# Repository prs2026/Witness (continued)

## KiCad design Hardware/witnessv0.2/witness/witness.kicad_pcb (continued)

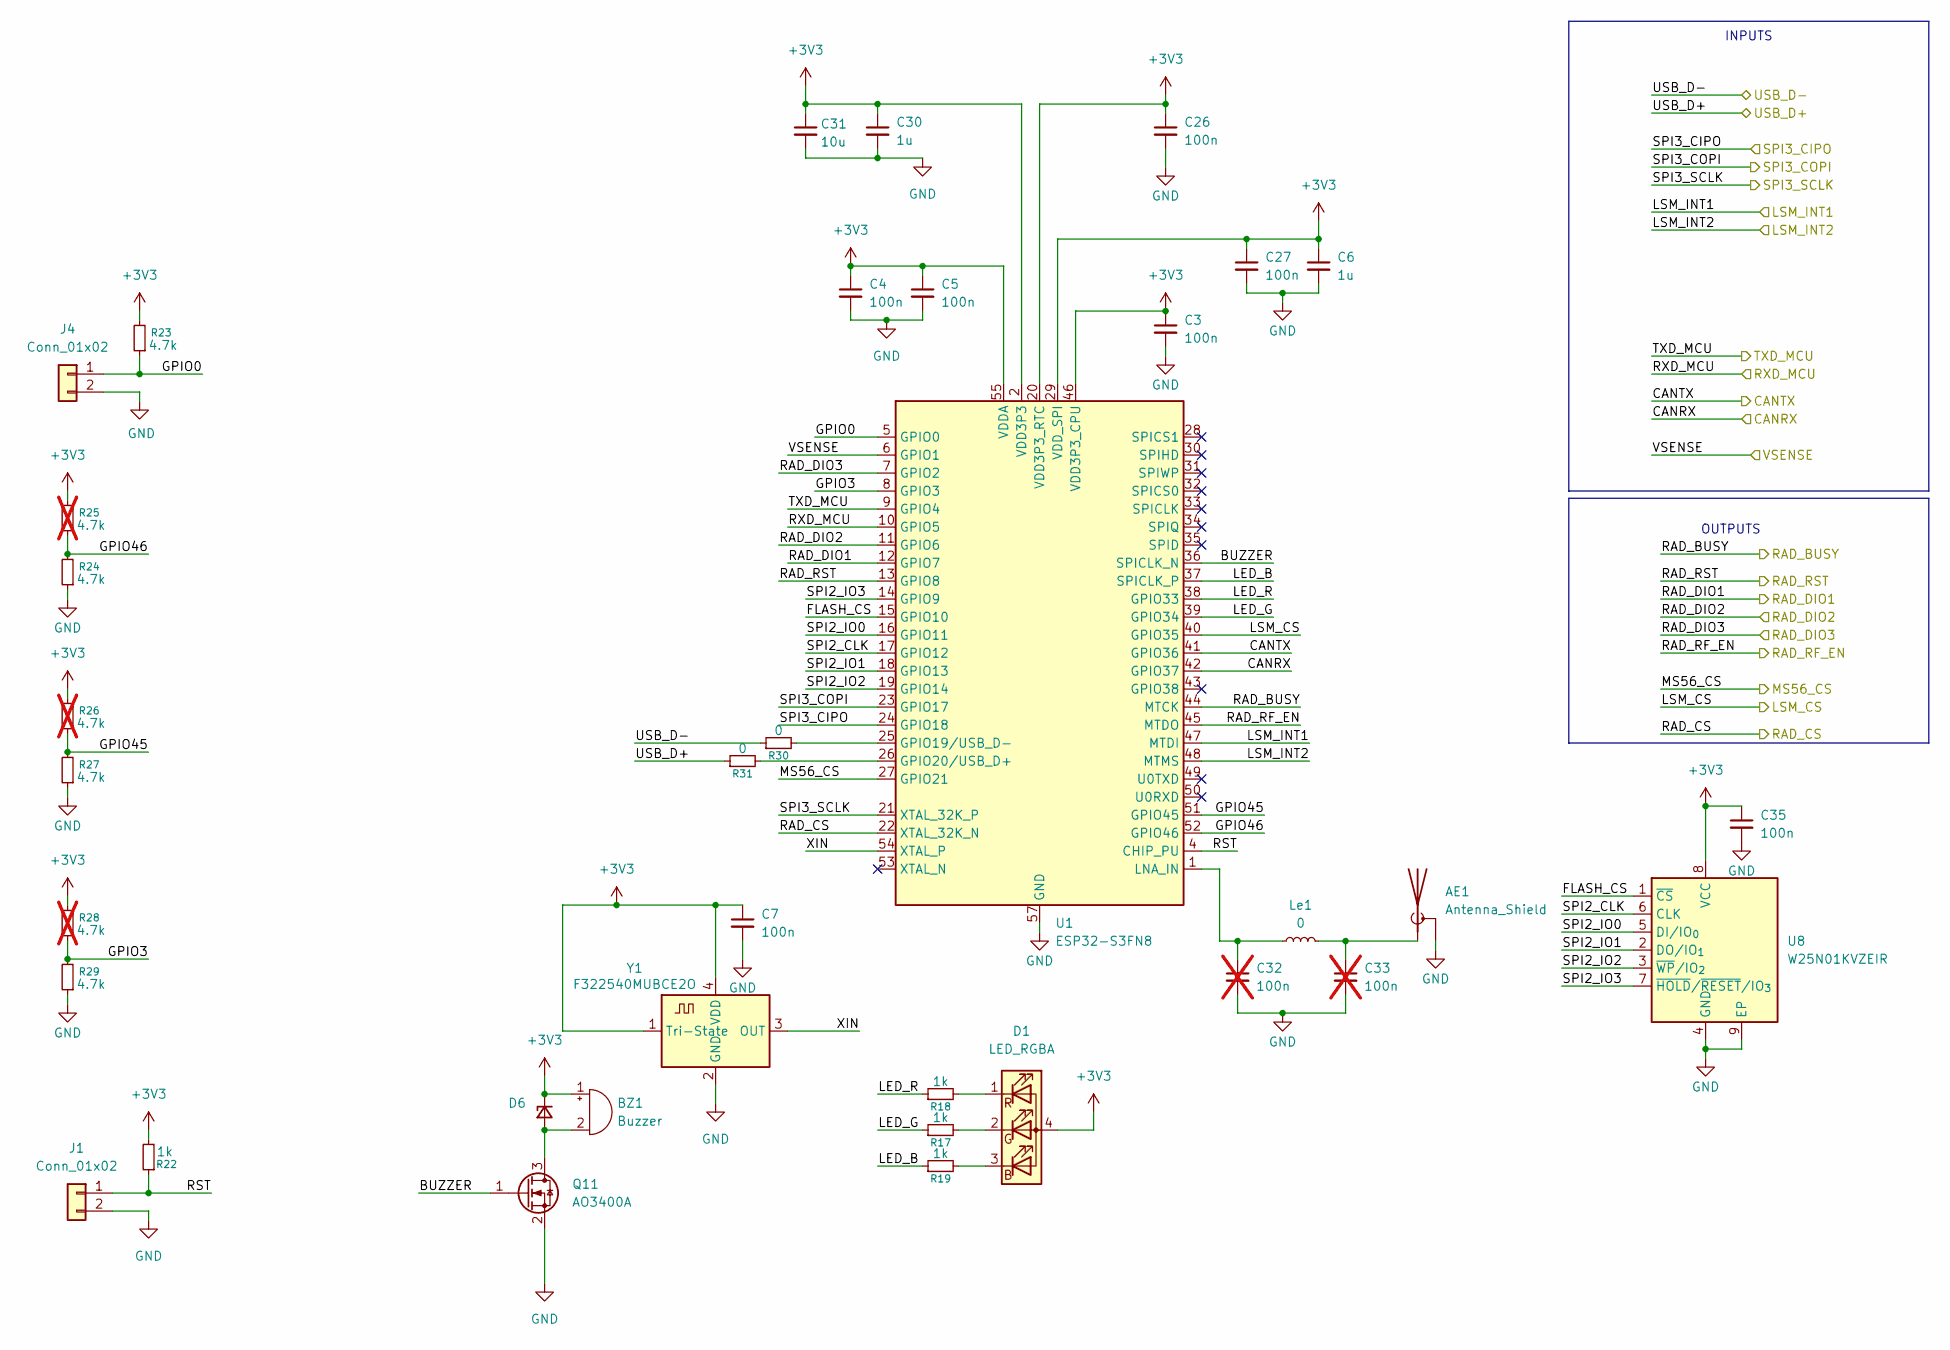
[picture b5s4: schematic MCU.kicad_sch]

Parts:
AE1: Antenna_Shield; U.FL_Molex_MCRF_73412-0110_Vertical
BZ1: Buzzer; OWMB-505020S-40-12D
C3, C4, C5, C7, C26, C27, C35: 100n; C_0402_1005Metric; LCSC_Part C307331
C6, C30: 1u; C_0402_1005Metric; LCSC_Part C52923
C31: 10u; C_0603_1608Metric; LCSC_Part C96446
C32, C33: 100n; C_0402_1005Metric; LCSC_Part C307331; not fitted
D1: LED_RGBA; 0603x2 RGB
D6: BZX584C10; D_SOD-523; LCSC_Part C22395577
J1, J4: Conn_01x02; SolderJumper-2_P1.3mm_Open_RoundedPad1.0x1.5mm
Le1: 0; L_0402_1005Metric
Q11: AO3400A; SOT-23; LCSC_Part C20917
R17, R18, R19, R22: 1k; R_0402_1005Metric; LCSC_Part C11702
R23, R24, R27, R29: 4.7k; R_0402_1005Metric; LCSC_Part C25900
R25, R26, R28: 4.7k; R_0402_1005Metric; LCSC_Part C25900; not fitted
R30, R31: 0; R_0402_1005Metric; LCSC_Part C17168
U1: ESP32-S3FN8; QFN-56-1EP_7x7mm_P0.4mm_EP4x4mm; LCSC_Part C2913196
U8: W25N01KVZEIR; WSON-8-1EP_8x6mm_P1.27mm_EP3.4x4.3mm; LCSC_Part C22472329
Y1: F322540MUBCE2O; Oscillator_SMD_Abracon_ASCO-4Pin_1.6x1.2mm; LCSC_Part C5917310

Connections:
+3V3: BZ1.1 (+), C3.1, C4.1, C5.1, C6.1, C7.1, C26.1, C27.1, C30.1, C31.1, C35.1, D1.4 (A), D6.1 (K), R22.2, R23.2, R25.2, R26.2, R28.2, U1.2 (VDD3P3), U1.3 (VDD3P3), U1.20 (VDD3P3_RTC), U1.29 (VDD_SPI), U1.46 (VDD3P3_CPU), U1.55 (VDDA), U1.56 (VDDA), U8.8 (VCC), Y1.1 (Tri-State), Y1.4 (VDD); also elsewhere on the board
/IO/USB_D+: R31.1; also elsewhere on the board
/IO/USB_D-: R30.1; also elsewhere on the board
/MCU/BUZZER: Q11.1 (G), U1.36 (SPICLK_N)
/MCU/CANRX: U1.42 (GPIO37); also elsewhere on the board
/MCU/CANTX: U1.41 (GPIO36); also elsewhere on the board
/MCU/FLASH_CS: U1.15 (GPIO10), U8.1 (~CS)
/MCU/GPIO0: J4.1, R23.1, U1.5 (GPIO0)
/MCU/GPIO3: R28.1, R29.2, U1.8 (GPIO3)
/MCU/GPIO45: R26.1, R27.2, U1.51 (GPIO45)
/MCU/GPIO46: R24.2, R25.1, U1.52 (GPIO46)
/MCU/LED_B: R19.1, U1.37 (SPICLK_P)
/MCU/LED_G: R17.1, U1.39 (GPIO34)
/MCU/LED_R: R18.1, U1.38 (GPIO33)
/MCU/LSM_CS: U1.40 (GPIO35); also elsewhere on the board
/MCU/LSM_INT1: U1.47 (MTDI); also elsewhere on the board
/MCU/LSM_INT2: U1.48 (MTMS); also elsewhere on the board
/MCU/MS56_CS: U1.27 (GPIO21); also elsewhere on the board
/MCU/RAD_BUSY: U1.44 (MTCK); also elsewhere on the board
/MCU/RAD_CS: U1.22 (XTAL_32K_N); also elsewhere on the board
/MCU/RAD_DIO1: U1.12 (GPIO7); also elsewhere on the board
/MCU/RAD_DIO2: U1.11 (GPIO6); also elsewhere on the board
/MCU/RAD_DIO3: U1.7 (GPIO2); also elsewhere on the board
/MCU/RAD_RF_EN: U1.45 (MTDO); also elsewhere on the board
/MCU/RAD_RST: U1.13 (GPIO8); also elsewhere on the board
/MCU/RST: J1.1, R22.1, U1.4 (CHIP_PU)
/MCU/RXD_MCU: U1.10 (GPIO5); also elsewhere on the board
/MCU/SPI2_CLK: U1.17 (GPIO12), U8.6 (CLK)
/MCU/SPI2_IO0: U1.16 (GPIO11), U8.5 (DI/IO_{0})
/MCU/SPI2_IO1: U1.18 (GPIO13), U8.2 (DO/IO_{1})
/MCU/SPI2_IO2: U1.19 (GPIO14), U8.3 (~WP/IO_{2})
/MCU/SPI2_IO3: U1.14 (GPIO9), U8.7 (~HOLD/~RESET/IO_{3})
/MCU/SPI3_CIPO: U1.24 (GPIO18); also elsewhere on the board
/MCU/SPI3_COPI: U1.23 (GPIO17); also elsewhere on the board
/MCU/SPI3_SCLK: U1.21 (XTAL_32K_P); also elsewhere on the board
/MCU/TXD_MCU: U1.9 (GPIO4); also elsewhere on the board
/MCU/VSENSE: U1.6 (GPIO1); also elsewhere on the board
/MCU/XIN: U1.54 (XTAL_P), Y1.3 (OUT)
GND: AE1.2 (Shield), C3.2, C4.2, C5.2, C6.2, C7.2, C26.2, C27.2, C30.2, C31.2, C32.2, C33.2, C35.2, J1.2, J4.2, Q11.2 (S), R24.1, R27.1, R29.1, U1.57 (GND), U8.4 (GND), U8.9 (EP), Y1.2 (GND); also elsewhere on the board
unnamed: AE1.1 (A), C33.1, Le1.2
unnamed: BZ1.2 (-), D6.2 (A), Q11.3 (D)
unnamed: D1.3 (BK), R19.2
unnamed: D1.2 (GK), R17.2
unnamed: D1.1 (RK), R18.2
unnamed: R30.2, U1.25 (GPIO19/USB_D-)
unnamed: R31.2, U1.26 (GPIO20/USB_D+)
unnamed: C32.1, Le1.1, U1.1 (LNA_IN)

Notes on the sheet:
OUTPUTS
INPUTS

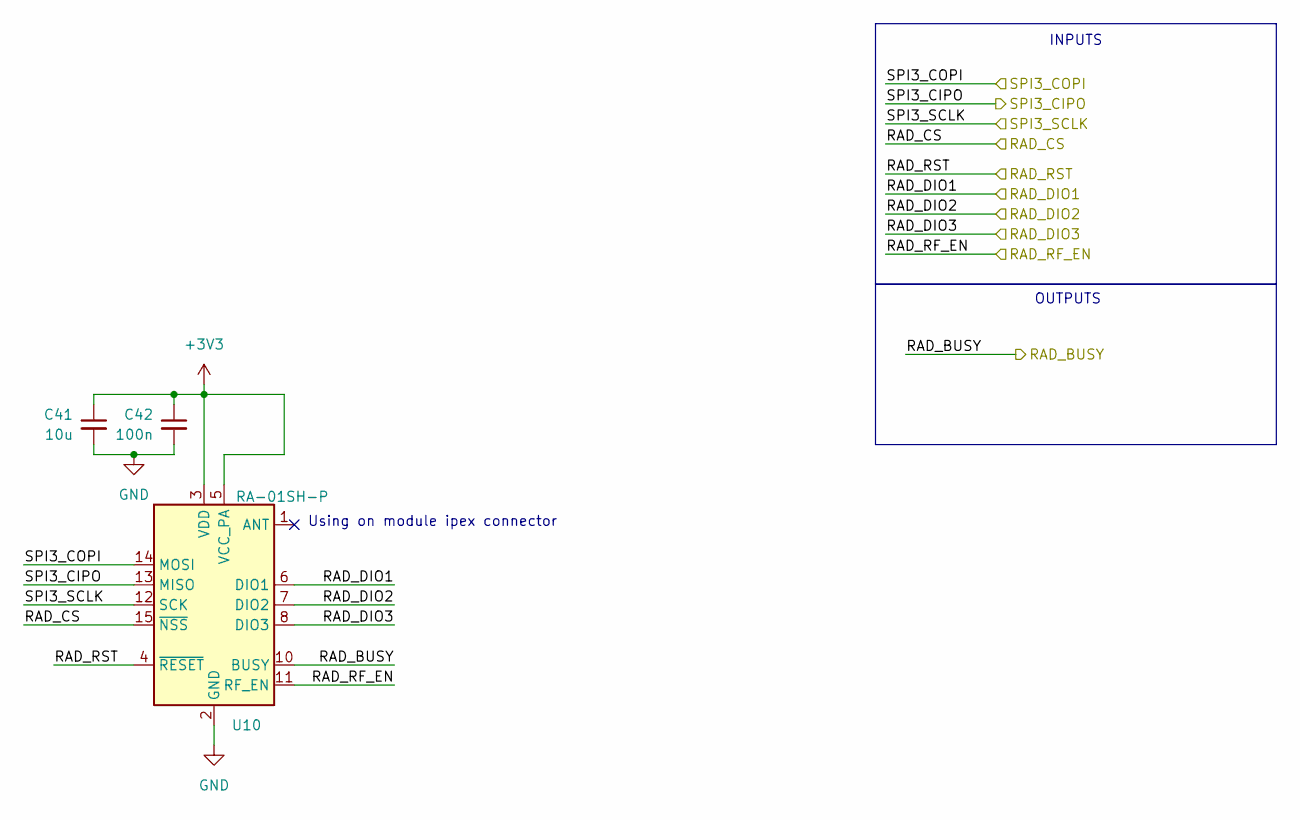
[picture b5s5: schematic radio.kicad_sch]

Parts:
C41: 10u; C_0603_1608Metric; LCSC_Part C96446
C42: 100n; C_0402_1005Metric; LCSC_Part C307331
U10: RA-01SH-P; Ai-Thinker-Ra-01-LoRa

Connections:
+3V3: C41.1, C42.1, U10.3 (VDD), U10.5 (VCC_PA); also elsewhere on the board
/MCU/RAD_BUSY: U10.10 (BUSY); also elsewhere on the board
/MCU/RAD_CS: U10.15 (~NSS); also elsewhere on the board
/MCU/RAD_DIO1: U10.6 (DIO1); also elsewhere on the board
/MCU/RAD_DIO2: U10.7 (DIO2); also elsewhere on the board
/MCU/RAD_DIO3: U10.8 (DIO3); also elsewhere on the board
/MCU/RAD_RF_EN: U10.11 (RF_EN); also elsewhere on the board
/MCU/RAD_RST: U10.4 (~RESET); also elsewhere on the board
/MCU/SPI3_CIPO: U10.13 (MISO); also elsewhere on the board
/MCU/SPI3_COPI: U10.14 (MOSI); also elsewhere on the board
/MCU/SPI3_SCLK: U10.12 (SCK); also elsewhere on the board
GND: C41.2, C42.2, U10.2 (GND), U10.9 (GND), U10.16 (GND); also elsewhere on the board

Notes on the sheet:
Using on module ipex connector
OUTPUTS
INPUTS

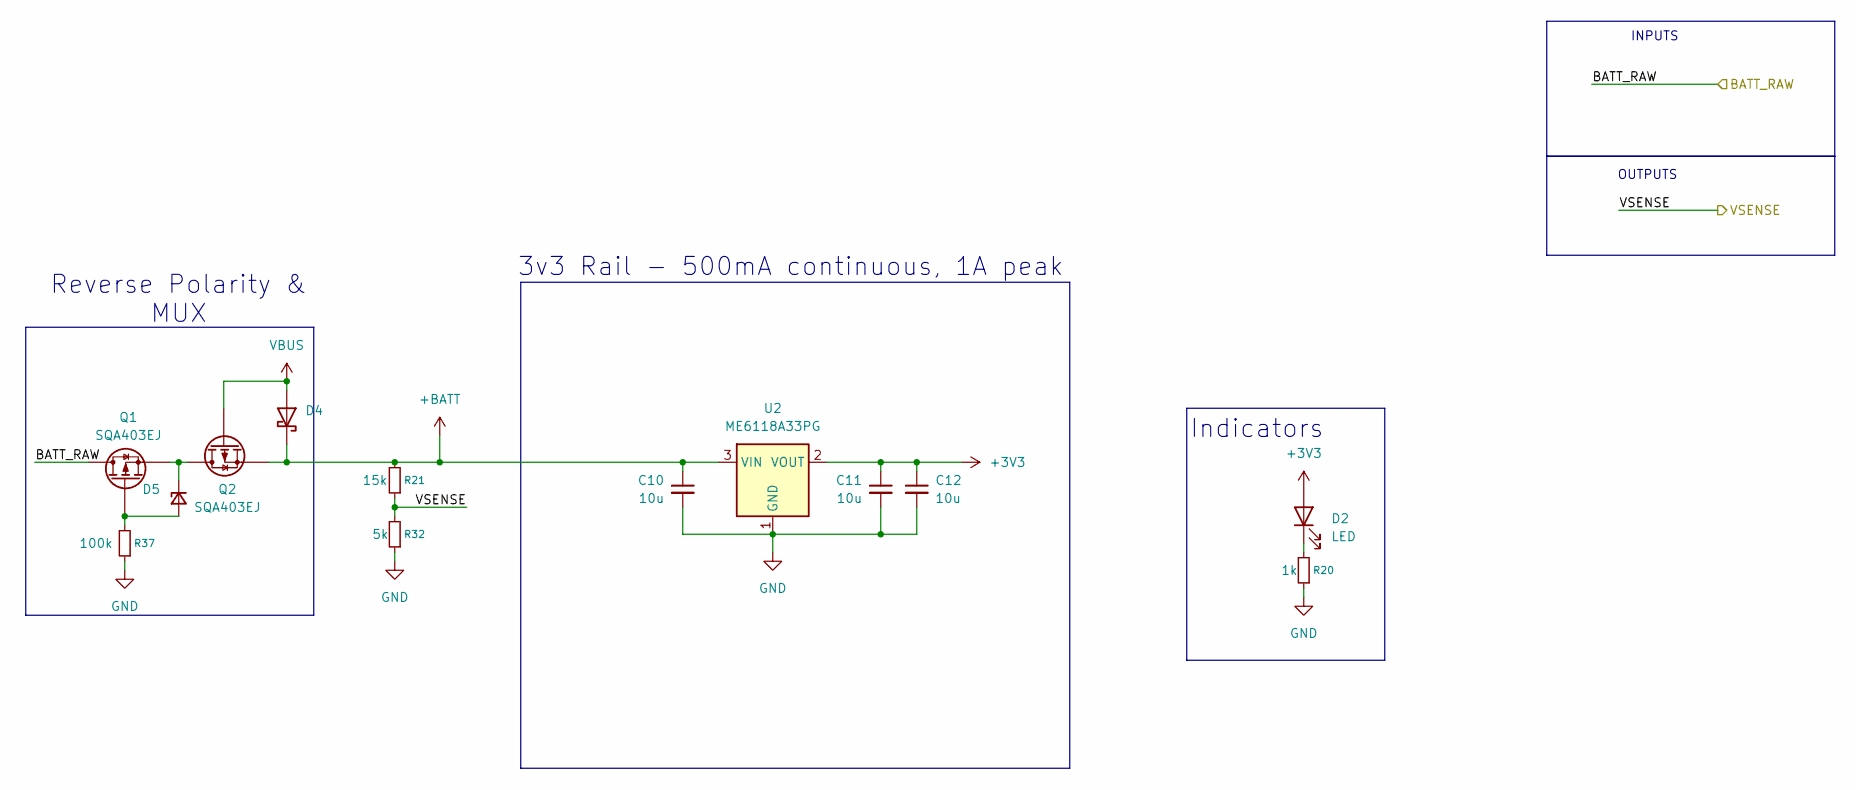
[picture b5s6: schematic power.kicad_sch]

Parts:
C10, C11, C12: 10u; C_0805_2012Metric; LCSC_Part C440198
D2: LED; LED_0603_1608Metric
D4: PMEG2020EH,115; D_SOD-123F; LCSC_Part C456104
D5: BZX584C10; D_SOD-523; LCSC_Part C22395577
Q1, Q2: SQA403EJ; Vishay_PowerPAK_SC70-6L_Single; LCSC_Part C7083947
R20: 1k; R_0402_1005Metric; LCSC_Part C11702
R21: 15k; R_0402_1005Metric
R32: 5k; R_0402_1005Metric
R37: 100k; R_0402_1005Metric
U2: ME6118A33PG; SOT-89-3; LCSC_Part C236721

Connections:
+3V3: C11.1, C12.1, D2.2 (A), U2.2 (VOUT); also elsewhere on the board
+BATT: C10.1, D4.1 (K), Q2.4 (S), R21.2, U2.3 (VIN)
/IO/BATT_RAW: Q1.1 (D); also elsewhere on the board
/MCU/VSENSE: R21.1, R32.2; also elsewhere on the board
GND: C10.2, C11.2, C12.2, R20.1, R32.1, R37.1, U2.1 (GND); also elsewhere on the board
unnamed: D2.1 (K), R20.2
unnamed: D5.2 (A), Q1.3 (G), R37.2
unnamed: D5.1 (K), Q1.4 (S), Q2.1 (D)
VBUS: D4.2 (A), Q2.3 (G); also elsewhere on the board

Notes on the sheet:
Indicators
OUTPUTS
INPUTS
Reverse Polarity & MUX
3v3 Rail - 500mA continuous, 1A peak

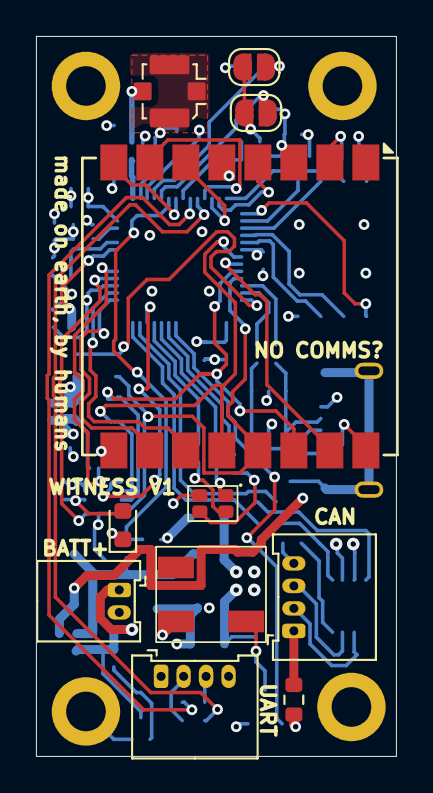
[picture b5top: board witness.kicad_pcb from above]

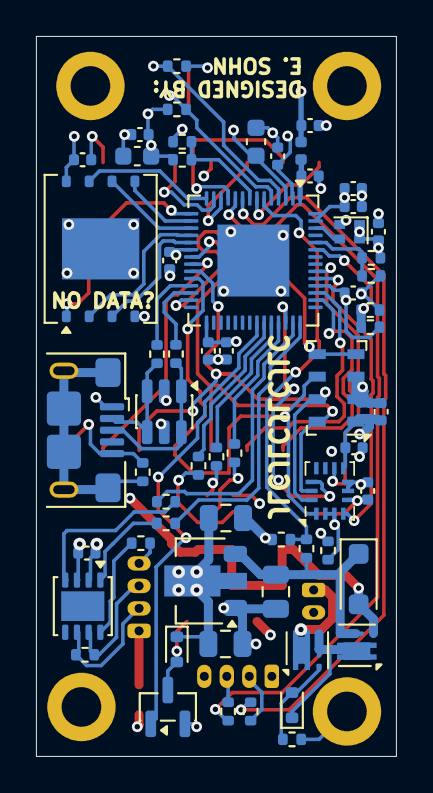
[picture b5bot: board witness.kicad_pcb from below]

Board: 4 copper layers, 20.0 x 40.0 mm, 76 parts (61 on the bottom side), 62 nets.

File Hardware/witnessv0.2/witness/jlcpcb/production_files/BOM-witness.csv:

Comment,Designator,Footprint,LCSC,Quantity
0,"R30,R31,R33,R34,R35,R36,R38,R51",R_0402_1005Metric,C17168,8
100n,"C26,C27,C28,C3,C35,C36,C37,C38,C4,C42,C5,C7",C_0402_1005Metric,C307331,12
10u,"C10,C11,C12",C_0805_2012Metric,C440198,3
10u,"C31,C41",C_0603_1608Metric,C96446,2
120,R39,R_0402_1005Metric,C25079,1
1k,"R17,R18,R19,R20,R22",R_0402_1005Metric,C11702,5
1u,"C30,C6",C_0402_1005Metric,C52923,2
4.7k,"R23,R24,R27,R29",R_0402_1005Metric,C25900,4
AO3400A,Q11,SOT-23,C20917,1
BZX584C10,"D5,D6",D_SOD-523,C22395577,2
ESP32-S3FN8,U1,QFN-56-1EP_7x7mm_P0.4mm_EP4x4mm,C2913196,1
F322540MUBCE2O,Y1,Oscillator_SMD_Abracon_ASCO-4Pin_1.6x1.2mm,C5917310,1
LSM6DSV320XTR,U4,Bosch_LGA-14_3x2.5mm_P0.5mm,C26633007,1
ME6118A33PG,U2,SOT-89-3,C236721,1
MS5607-02BA,U7,LGA-8_3x5mm_P1.25mm,C97627,1
"PMEG2020EH,115",D4,D_SOD-123F,C456104,1
SQA403EJ,"Q1,Q2",Vishay_PowerPAK_SC70-6L_Single,C7083947,2
TCAN1044A-Q1,U5,VSON-8-1EP_3x3mm_P0.65mm_EP1.65x2.4mm,C3234119,1
USBLC6-2SC6,U9,SOT-23-6,C7519,1
USB_B_Micro,J3,USB_Micro-B_Amphenol_10118193-0002LF_Horizontal,C132562,1
W25N01KVZEIR,U8,WSON-8-1EP_8x6mm_P1.27mm_EP3.4x4.3mm,C22472329,1
RA-01SH-P,U10,Ai-Thinker-Ra-01-LoRa,,1
Conn_01x02,J4,SolderJumper-2_P1.3mm_Open_RoundedPad1.0x1.5mm,,1
Conn_01x04,J5,Molex_MicroLock-2200980471-01x04-Horizontal,,1
Conn_01x02,J1,SolderJumper-2_P1.3mm_Open_RoundedPad1.0x1.5mm,,1
Conn_01x04,J6,Molex_MicroLock-2200980471-01x04-Horizontal,,1
MountingHole_Pad,H6,MountingHole_2.2mm_M2_DIN965_Pad,,1
MountingHole_Pad,H5,MountingHole_2.2mm_M2_DIN965_Pad,,1
LED_RGBA,D1,0603x2 RGB,,1
Conn_01x02,J2,Molex_Micro_Lock_2200980271_01x02_Horizontal,,1
MountingHole_Pad,H7,MountingHole_2.2mm_M2_DIN965_Pad,,1
Buzzer,BZ1,OWMB-505020S-40-12D,,1
LED,D2,LED_0603_1608Metric,,1
MountingHole_Pad,H4,MountingHole_2.2mm_M2_DIN965_Pad,,1
Antenna_Shield,AE1,U.FL_Molex_MCRF_73412-0110_Vertical,,1
15k,R21,R_0402_1005Metric,,1
100k,R37,R_0402_1005Metric,,1
5k,R32,R_0402_1005Metric,,1
0,R13,R_0603_1608Metric,,1
0,Le1,L_0402_1005Metric,,1

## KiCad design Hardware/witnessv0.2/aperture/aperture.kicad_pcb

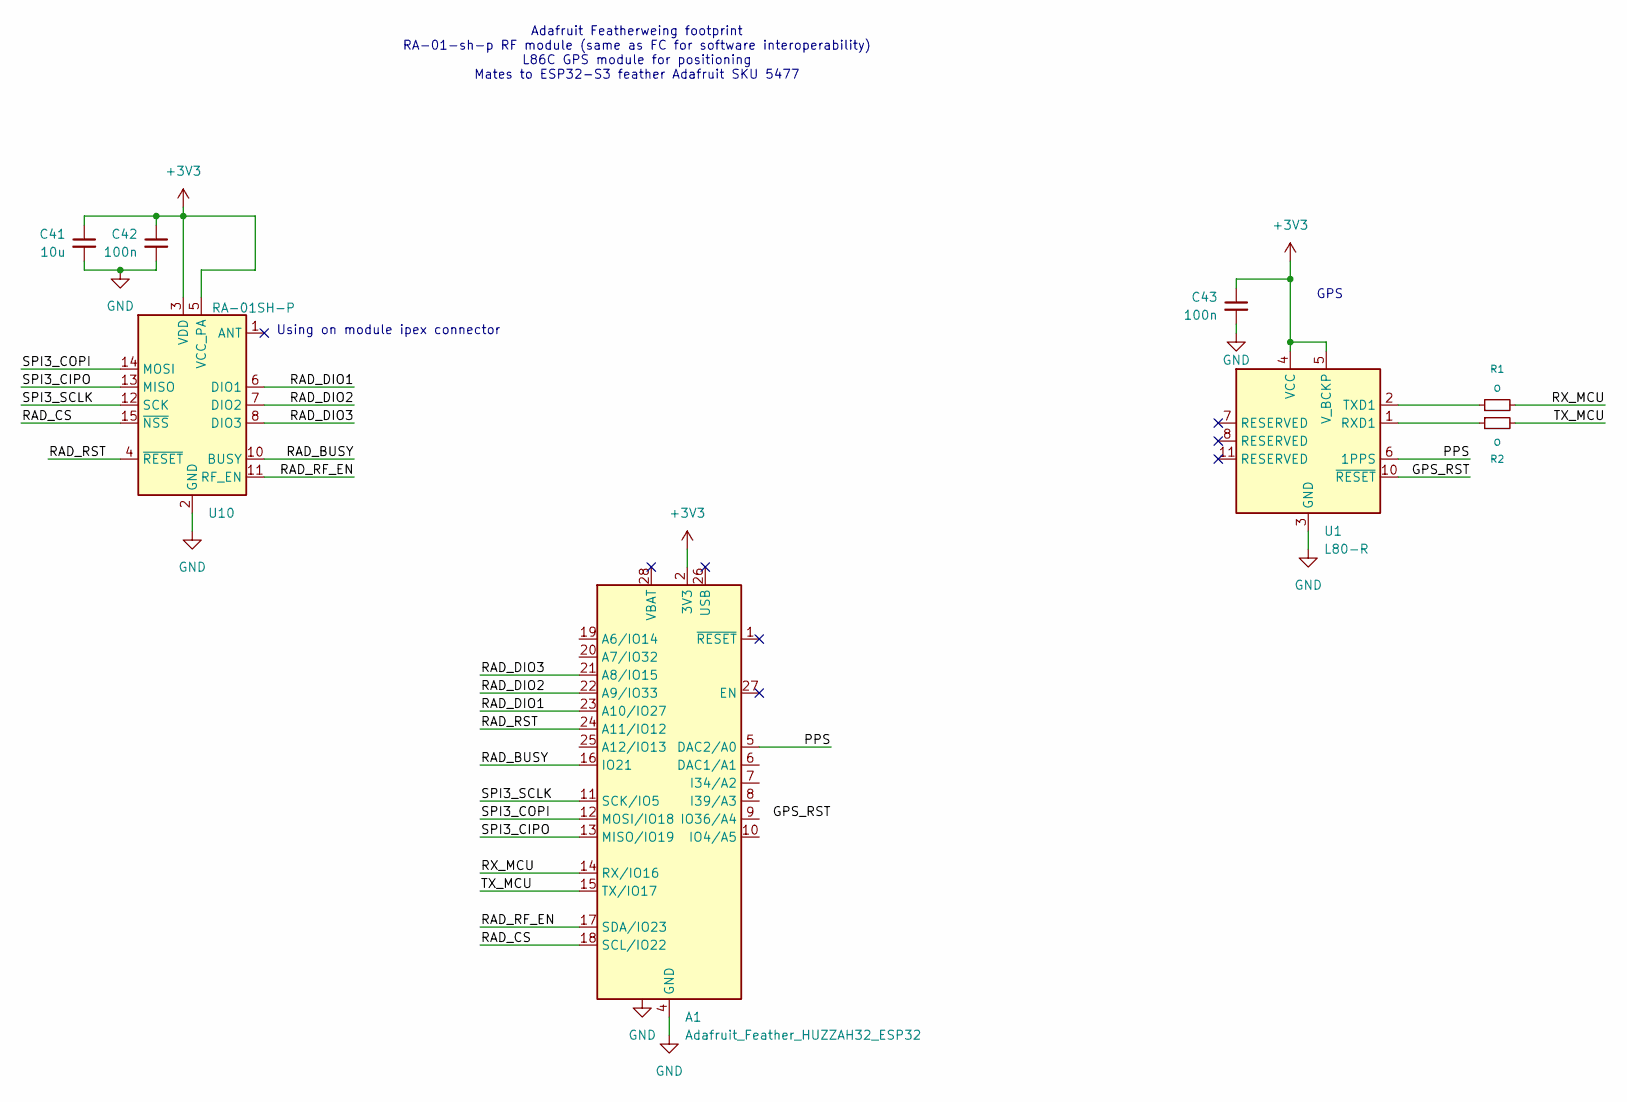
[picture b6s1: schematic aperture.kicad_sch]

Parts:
A1: Adafruit_Feather_HUZZAH32_ESP32; Adafruit_Feather
C41: 10u; C_0603_1608Metric; LCSC_Part C96446
C42, C43: 100n; C_0603_1608Metric; LCSC_Part C96446
R1, R2: o; R_0603_1608Metric
U1: L80-R; Quectel_L80-R
U10: RA-01SH-P; Ai-Thinker-Ra-01-LoRa

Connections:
+3V3: A1.2 (3V3), C41.1, C42.1, C43.1, U1.4 (VCC), U1.5 (V_BCKP), U10.3 (VDD), U10.5 (VCC_PA)
/GPS_RST: A1.9 (IO36/A4), U1.10 (~RESET)
/PPS: A1.5 (DAC2/A0), U1.6 (1PPS)
/RAD_BUSY: A1.16 (IO21), U10.10 (BUSY)
/RAD_CS: A1.18 (SCL/IO22), U10.15 (~NSS)
/RAD_DIO1: A1.23 (A10/IO27), U10.6 (DIO1)
/RAD_DIO2: A1.22 (A9/IO33), U10.7 (DIO2)
/RAD_DIO3: A1.21 (A8/IO15), U10.8 (DIO3)
/RAD_RF_EN: A1.17 (SDA/IO23), U10.11 (RF_EN)
/RAD_RST: A1.24 (A11/IO12), U10.4 (~RESET)
/RX_MCU: A1.14 (RX/IO16), R1.2
/SPI3_CIPO: A1.13 (MISO/IO19), U10.13 (MISO)
/SPI3_COPI: A1.12 (MOSI/IO18), U10.14 (MOSI)
/SPI3_SCLK: A1.11 (SCK/IO5), U10.12 (SCK)
/TX_MCU: A1.15 (TX/IO17), R2.2
GND: A1.4 (GND), C41.2, C42.2, C43.2, U1.3 (GND), U1.12 (GND), U10.2 (GND), U10.9 (GND), U10.16 (GND)
unnamed: R2.1, U1.1 (RXD1)
unnamed: R1.1, U1.2 (TXD1)

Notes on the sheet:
GPS
Using on module ipex connector
Adafruit Featherweing footprint RA-01-sh-p RF module (same as FC for software interoperability) L86C GPS module for positioning Mates to ESP32-S3 feather Adafruit SKU 5477

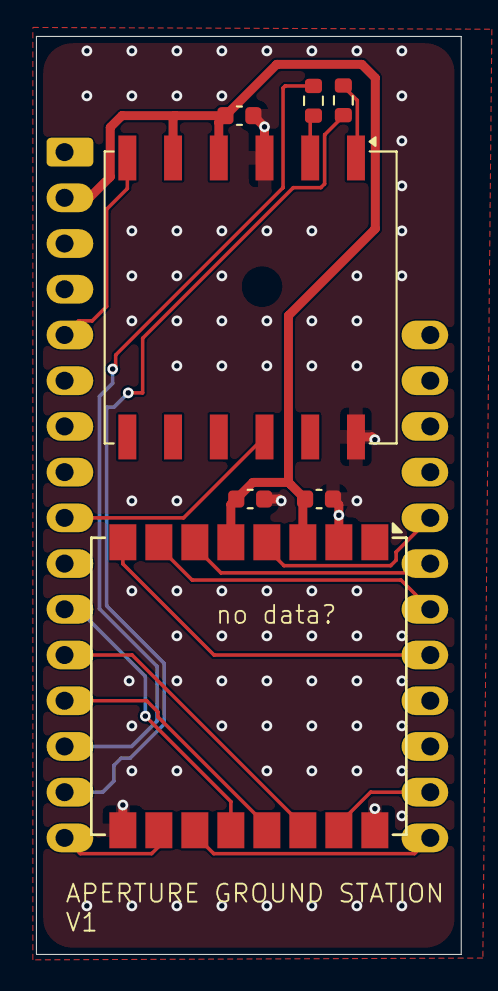
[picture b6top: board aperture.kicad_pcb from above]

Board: 2 copper layers, 23.6 x 51.0 mm, 8 parts (0 on the bottom side), 18 nets.

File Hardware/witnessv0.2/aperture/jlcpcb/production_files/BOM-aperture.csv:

Comment,Designator,Footprint,LCSC,Quantity
100n,"C42,C43",C_0603_1608Metric,C96446,2
10u,C41,C_0603_1608Metric,C96446,1
Adafruit_Feather_HUZZAH32_ESP32,A1,Adafruit_Feather,,1
L80-R,U1,Quectel_L80-R,,1
o,R1,R_0603_1608Metric,,1
RA-01SH-P,U10,Ai-Thinker-Ra-01-LoRa,,1
o,R2,R_0603_1608Metric,,1

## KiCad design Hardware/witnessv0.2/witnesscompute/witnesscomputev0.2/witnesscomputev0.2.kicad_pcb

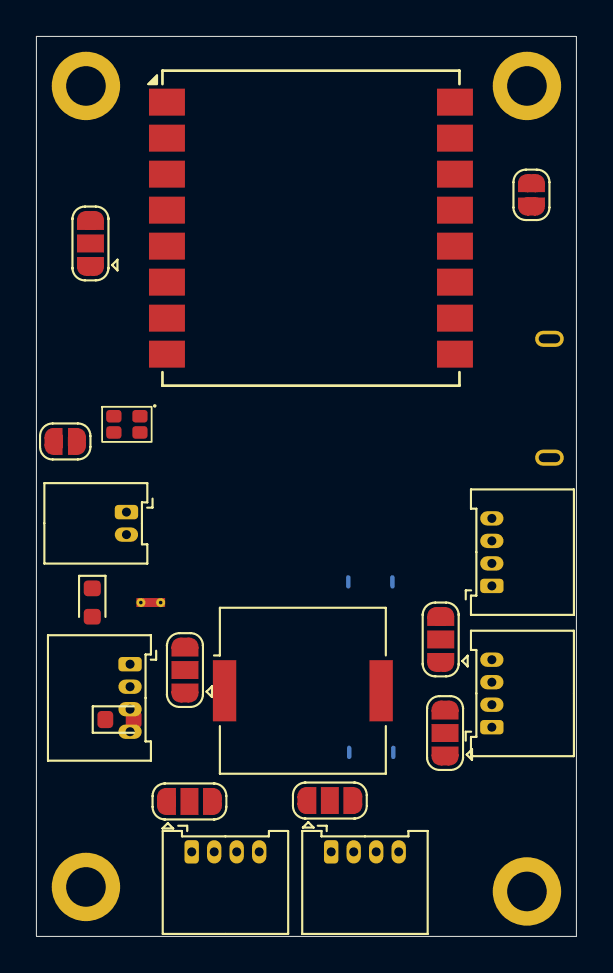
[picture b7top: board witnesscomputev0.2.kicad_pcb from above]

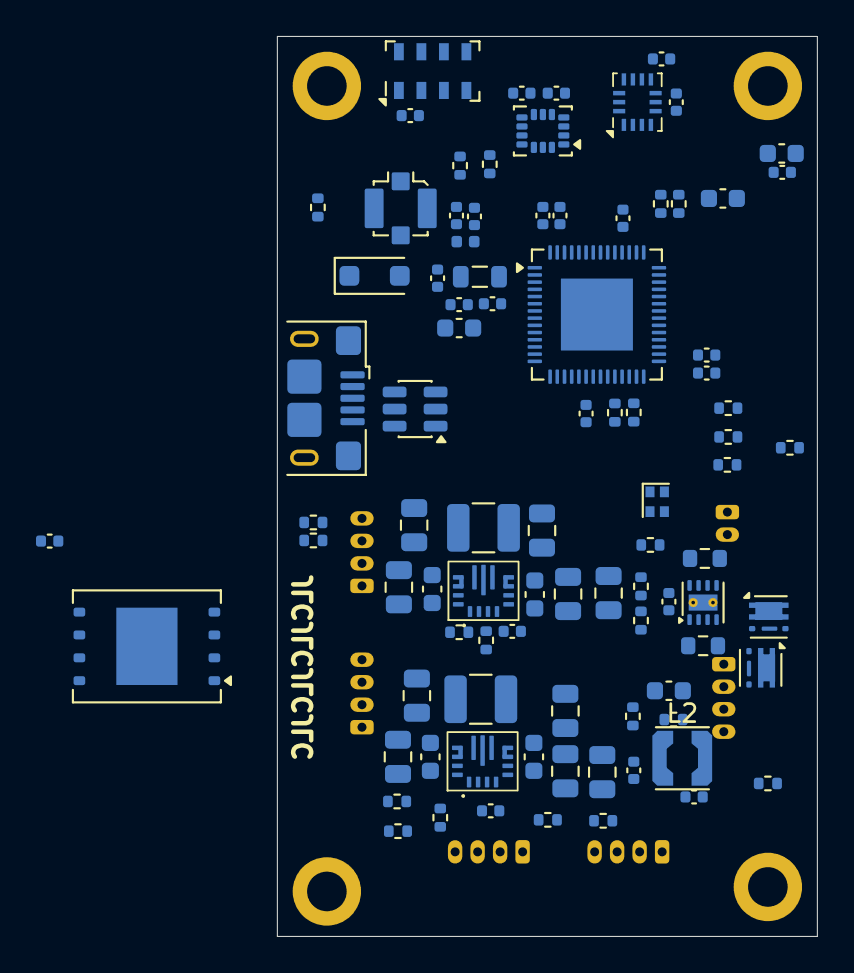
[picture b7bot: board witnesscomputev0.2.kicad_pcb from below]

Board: 4 copper layers, 30.0 x 50.0 mm, 112 parts (89 on the bottom side), 58 nets, no tracks yet.

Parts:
AE1: Antenna_Shield; U.FL_Molex_MCRF_73412-0110_Vertical
BZ1: Buzzer; Buzzer_Murata_PKMCS0909E
C3, C4, C5, C7, C15, C16, C21, C26, C27, C28, C29, C32, C33, C34, C35, C36, C37, C38, C39, C40, C42: 100n; C_0402_1005Metric
C6, C30: 1u; C_0402_1005Metric
C8, C9, C20, C22, C31, C41, C43: 10u; C_0603_1608Metric
C10, C11, C18, C19: 10u; C_0805_2012Metric
C12, C13, C14, C23, C24, C25: 22u; C_0805_2012Metric
C17: 470n; C_0603_1608Metric
D1: LED_RGBA; 0603x2 RGB
D2, D3: LED; LED_0603_1608Metric
D4: PMEG2020EH,115; D_SOD-123F
H4, H5, H6, H7: MountingHole_Pad; MountingHole_2.2mm_M2_DIN965_Pad
J1, J4: Conn_01x02; SolderJumper-2_P1.3mm_Open_RoundedPad1.0x1.5mm
J2: Conn_01x02; Molex_Micro_Lock_2200980271_01x02_Horizontal
J3: USB_B_Micro; USB_Micro-B_Amphenol_10118193-0002LF_Horizontal
J5, J6, J7, J8, J9: Conn_01x04; Molex_MicroLock-2200980471-01x04-Horizontal
JP1, JP2, JP3, JP4, JP5, JP6: SolderJumper_3_Open; SolderJumper-3_P1.3mm_Open_RoundedPad1.0x1.5mm
L1, L3: 1u; L_1210_3225Metric
L2: 2.2u; L_Coilcraft_LPS3010
L4: 10n; L_0805_2012Metric
L5: L_Small; L_0402_1005Metric
Q1, Q2: SQA403EJ; Vishay_PowerPAK_SC70-6L_Single
R1, R9: 100k; R_0402_1005Metric
R2: 470k; R_0402_1005Metric
R3: 150k; R_0402_1005Metric
R5: 4.7; R_0402_1005Metric
R6, R10, R12: 10k; R_0402_1005Metric
R7: 680k; R_0402_1005Metric
R8: 130k; R_0402_1005Metric
R11: 35k; R_0402_1005Metric
R17, R18, R19, R20, R21, R22: 1k; R_0402_1005Metric
R23, R24, R25, R26, R27, R28, R29: 4.7k; R_0402_1005Metric
R30, R31: 0; R_0402_1005Metric
R33, R34: 2.5m; R_0603_1608Metric
U1: ESP32-S3FN8; QFN-56-1EP_7x7mm_P0.4mm_EP4x4mm
U2, U6: TPS63070; RNM0015A
U3: INA2180A3IDSG; Texas_DSG0008A_WSON-8-1EP_2x2mm_P0.5mm_EP0.9x1.6mm_ThermalV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
U4: LSM6DSV320XTR; Bosch_LGA-14_3x2.5mm_P0.5mm
U5: ICM-45686; LGA-14_3x2.5mm_P0.5mm_LayoutBorder3x4y
U7: MS5607-02BA; LGA-8_3x5mm_P1.25mm
U8: W25N01KVZEIR; WSON-8-1EP_8x6mm_P1.27mm_EP3.4x4.3mm
U9: USBLC6-2SC6; SOT-23-6
U10: RA-01SH-P; Ai-Thinker-Ra-01-LoRa
Y1: F322540MUBCE2O; Oscillator_SMD_Abracon_ASCO-4Pin_1.6x1.2mm

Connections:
+3V3: C3.1, C4.1, C5.1, C6.1, C16.1, C26.1, C27.1, C29.1, C30.1, C31.1, C34.1, C35.1, C36.1, C37.1, C38.1, C39.1, C40.1, C41.1, C42.1, D1.4 (A), D2.2 (A), JP1.3 (B), JP2.3 (B), JP3.3 (B), JP4.3 (B), JP5.3 (B), JP6.1 (A), L2.2, L4.1, R5.1, R22.2, R23.2, R25.2, R26.2, R28.2, U1.20 (VDD3P3_RTC), U1.29 (VDD_SPI), U1.46 (VDD3P3_CPU), U1.55 (VDDA), U1.56 (VDDA), U3.8 (VS), U4.5 (VDDIO), U4.8 (VDD), U5.5 (VDDIO), U5.8 (VDD), U7.1 (VDD), U8.8 (VCC), U10.3 (VDD), Y1.1 (Tri-State), Y1.4 (VDD)
+5V: D3.2 (A), JP1.1 (A), JP2.1 (A), JP3.1 (A), JP4.1 (A), JP5.1 (A), JP6.3 (B), R34.2, U3.6 (-)
+BATT: J2.1, Q2.1 (D)
/IO/RXD_MCU: J5.3, J7.3, J8.3, J9.3
/IO/TXD_MCU: J5.2, J7.2, J8.2, J9.2
/IO/USB_D+: U9.1 (I/O1), U9.3 (I/O2)
/MCU/GPIO0: J4.1, R23.1, U1.5 (GPIO0)
/MCU/GPIO3: R28.1, R29.2, U1.8 (GPIO3)
/MCU/GPIO45: R26.1, R27.2, U1.51 (GPIO45)
/MCU/GPIO46: R24.2, R25.1, U1.52 (GPIO46)
/MCU/RST: J1.1, R22.1, U1.4 (CHIP_PU)
/MCU/SPI3_IO3: U8.3 (~WP/IO_{2}), U8.7 (~HOLD/~RESET/IO_{3})
/MCU/XIN: U1.54 (XTAL_P), Y1.3 (OUT)
/Power/5VSENSE+: C22.1, C23.1, C24.1, C25.1, R7.1, R9.1, R34.1, U3.5 (+), U6.7 (VOUT), U6.8 (VOUT)
/Power/BATT_POSTSW: C9.1, C10.1, C11.1, C18.1, C19.1, C20.1, R6.1, R11.1, R12.1, R33.2, U2.12 (VIN), U2.13 (VIN), U3.2 (-), U6.12 (VIN), U6.13 (VIN)
/Power/ISENSE+: Q1.4 (S), R33.1, U3.3 (+)
/Sensors/I2C_SCL: U4.13 (SCL), U5.3 (MAS_CLK)
/Sensors/I2C_SDA: U4.14 (SDA), U5.2 (MAS_DA)
/Sensors/MS56_CS: U7.4 (CSB), U7.5 (CSB)
/Sensors/SPI1_CIPO: U4.1 (SDO/SA0), U5.1 (AP_SDO), U7.6 (SDO)
/Sensors/SPI1_COPI: U4.3 (SCX), U5.14 (AP_SDIO), U7.7 (SDI/SDA)
/Sensors/SPI1_SCLK: U4.2 (SDX), U5.11 (AP_SCLK), U7.8 (SCLK)
GND: AE1.2 (Shield), BZ1.2 (-), C3.2, C4.2, C5.2, C6.2, C7.2, C8.2, C9.2, C10.2, C11.2, C12.2, C13.2, C14.2, C15.2, C16.2, C17.2, C18.2, C19.2, C20.2, C21.2, C22.2, C23.2, C24.2, C25.2, C26.2, C27.2, C28.2, C29.2, C30.2, C31.2, C32.2, C33.2, C34.2, C35.2, C36.2, C37.2, C38.2, C39.2, C40.2, C41.2, C42.2, C43.1, H4.1 (1_1), H5.1 (1_1), H6.1 (1_1), H7.1 (1_1), J1.2, J2.2, J3.5 (GND), J4.2, J5.4, J6.4, J7.4, J8.4, J9.4, Q1.3 (G), R3.2, R8.2, R10.2, R20.1, R21.1, R24.1, R27.1, R29.1, U1.57 (GND), U2.4 (GND), U2.6 (FB2), U2.10 (PGND), U2.15 (VSEL), U3.4 (GND), U3.9 (EP), U4.6 (GND), U4.7 (GND), U5.6 (GND), U6.4 (GND), U6.6 (FB2), U6.10 (PGND), U6.15 (VSEL), U7.2 (PS), U7.3 (GND), U8.4 (GND), U9.2 (GND), U10.2 (GND), U10.9 (GND), U10.16 (GND), Y1.2 (GND)
unnamed: AE1.1 (A), C33.1, L5.2
unnamed: C8.1, C12.1, C13.1, C14.1, C15.1, L2.1, R1.1, R2.1, U2.7 (VOUT), U2.8 (VOUT)
unnamed: C17.1, R5.2
unnamed: C28.1, L4.2, U1.2 (VDD3P3), U1.3 (VDD3P3)
unnamed: D1.3 (BK), R19.2
unnamed: D1.2 (GK), R17.2
unnamed: D1.1 (RK), R18.2
unnamed: D2.1 (K), R20.2
unnamed: D3.1 (K), R21.2
unnamed: D4.1 (K), Q1.1 (D), Q2.4 (S)
unnamed: J3.3 (D+), U9.6 (I/O1)
unnamed: J3.2 (D-), U9.4 (I/O2)
unnamed: J5.1, JP1.2 (C)
unnamed: J6.1, JP2.2 (C)
unnamed: J7.1, JP3.2 (C)
unnamed: J8.1, JP4.2 (C)
unnamed: J9.1, JP5.2 (C)
unnamed: C43.2, JP6.2 (C), U10.5 (VCC_PA)
unnamed: R30.2, U1.25 (GPIO19/USB_D-)
unnamed: R31.2, U1.26 (GPIO20/USB_D+)
unnamed: C32.1, L5.1, U1.1 (LNA_IN)
unnamed: R10.1, R11.2, U2.14 (EN)
unnamed: R2.2, R3.1, U2.5 (FB)
unnamed: L1.1, U2.11 (L1)
unnamed: L1.2, U2.9 (L2)
unnamed: R1.2, U2.2 (PG)
unnamed: R12.2, U2.1 (PS/SYNC)
unnamed: C7.1, U2.3 (VAUX)
unnamed: R7.2, R8.1, U6.5 (FB)
unnamed: L3.1, U6.11 (L1)
unnamed: L3.2, U6.9 (L2)
unnamed: R9.2, U6.2 (PG)
unnamed: R6.2, U6.1 (PS/SYNC)
unnamed: C21.1, U6.3 (VAUX)
VBUS: D4.2 (A), J3.1 (VBUS), Q2.3 (G), U9.5 (VBUS)

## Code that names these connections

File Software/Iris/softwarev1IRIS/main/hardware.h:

#pragma once

#include "driver/gpio.h"
#include "driver/uart.h"

// Iris ESP32-C3FH4 board pin map.
// Keep all physical board connections here so application code does not use
// raw GPIO numbers.
#define IRIS_PIN_VSENSE GPIO_NUM_0
// The PCB net labels at U5 are reversed: the TCAN3414 TXD input is on the
// net named CANRX (GPIO3), and its RXD output is on CAN_TX (GPIO1). These
// definitions describe the TWAI signal direction, not the schematic net name.
#define IRIS_PIN_CAN_TX GPIO_NUM_3
#define IRIS_PIN_BUTTON GPIO_NUM_2
#define IRIS_PIN_CAN_RX GPIO_NUM_1
#define IRIS_PIN_I2C_SDA GPIO_NUM_4
#define IRIS_PIN_I2C_SCL GPIO_NUM_5
#define IRIS_PIN_UART1_TX GPIO_NUM_6
#define IRIS_PIN_UART1_RX GPIO_NUM_7
#define IRIS_PIN_LED_RED GPIO_NUM_8
#define IRIS_PIN_LOAD_SWITCH_ENABLE GPIO_NUM_9
#define IRIS_PIN_LED_GREEN GPIO_NUM_10
#define IRIS_PIN_USB_D_MINUS GPIO_NUM_18
#define IRIS_PIN_USB_D_PLUS GPIO_NUM_19
#define IRIS_PIN_UART0_RX GPIO_NUM_20
#define IRIS_PIN_UART0_TX GPIO_NUM_21

// UART1 is the secondary packet transport. Complete application packets are
// sent directly as byte streams using the same framing as USB.
#define IRIS_UART1_PORT UART_NUM_1
#define IRIS_UART1_BAUD_RATE 115200U

// ESP32-C3 Classical CAN controller connected to the 3.3 V TCAN3414.
// STB (pin 8) is strapped low; SHDN (pin 5) may use its internal pulldown.
// Both ESP32 peers use Classical CAN, not CAN FD, despite transceiver FD support.
#define IRIS_TWAI_BITRATE 500000U

// Battery voltage monitor on GPIO0/ADC1 channel 0. The battery is connected
// through a 15 kohm high-side and 5 kohm low-side divider (4:1 ratio).
#define IRIS_BATTERY_DIVIDER_HIGH_OHMS 15000U
#define IRIS_BATTERY_DIVIDER_LOW_OHMS 5000U
#define IRIS_BATTERY_ADC_SAMPLE_COUNT 16U
#define IRIS_BATTERY_VOLTAGE_READ_INTERVAL_MS 1000U

// MCP23008 I/O expander. A2:A0 are tied low, giving address 0x20.
#define IRIS_MCP23008_I2C_ADDRESS 0x20U
#define IRIS_MCP23008_PIN_OUT1_ENABLE 0U
#define IRIS_MCP23008_PIN_OUT2_ENABLE 1U
#define IRIS_MCP23008_PIN_OUT3_ENABLE 2U
#define IRIS_MCP23008_PIN_5V_ENABLE 3U
#define IRIS_MCP23008_PIN_LED_BLUE 7U

#define IRIS_MCP23008_MASK_OUT1_ENABLE \
    (1U << IRIS_MCP23008_PIN_OUT1_ENABLE)
#define IRIS_MCP23008_MASK_OUT2_ENABLE \
    (1U << IRIS_MCP23008_PIN_OUT2_ENABLE)
#define IRIS_MCP23008_MASK_OUT3_ENABLE \
    (1U << IRIS_MCP23008_PIN_OUT3_ENABLE)
#define IRIS_MCP23008_MASK_5V_ENABLE \
    (1U << IRIS_MCP23008_PIN_5V_ENABLE)
#define IRIS_MCP23008_MASK_LED_BLUE \
    (1U << IRIS_MCP23008_PIN_LED_BLUE)

// The expander RESET input shares the LS_EN net.
#define IRIS_PIN_MCP23008_RESET IRIS_PIN_LOAD_SWITCH_ENABLE

// PAC193x current monitor. ADDRSEL is tied to ground. Channels 1-3 each
// use a 20 milliohm shunt on the Iris board.
#define IRIS_PAC1931_I2C_ADDRESS 0x10U
#define IRIS_PAC1931_CHANNEL_COUNT 3U
#define IRIS_PAC1931_SENSE_RESISTOR_MICROOHMS 20000U
// Empirical board calibration: measured currents are five times the applied
// current when converted using only the nominal 20 milliohm shunt value.
#define IRIS_PAC1931_CURRENT_CALIBRATION_DIVISOR 5U
